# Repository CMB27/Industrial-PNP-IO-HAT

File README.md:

# Industrial PNP IO HAT+ for Raspberry Pi

Many industrial sensors, actuators, and indicator lights use 24V digital signals.
The [GPIO on the Raspberry PI 40-pin header](https://pinout.xyz/), are strictly 3.3V and not directly compatible with these devices.
This board adapts the GPIO on the Raspberry Pi to be able to interface with these higher voltage signals.

Industrial 24V signals come in two main flavors: PNP and NPN.
PNP signals are **on** when connected to 24VDC and **off** when disconnected (left floating).
NPN signals are **on** when connected to 0V (GND) and **off** when disconnected.

Where I live and work PNP signals are overwhelmingly more popular.
They are also a bit more intuitive for most people.
The digital inputs and outputs on this board are for PNP signals.

This IO board is designed to mount to DIN rail.
DIN rail is the dominant electronics mounting system in industry.
It comes in several varieties, but the most common is DIN 3 also known as "top hat".
This system is primarily designed to work with DIN 3 rail.

This board conforms to the [Raspberry Pi HAT+ specification](https://pip-assets.raspberrypi.com/categories/1215-raspberry-pi-hat/documents/RP-008281-DS-1-hat-plus-specification.pdf)

## Components

### Custom Components (The Circuit Board)
The circuit board can be ordered from [OSH Park](https://oshpark.com/shared_projects/fHu9WALf).
Gerber and Excellon drill files are also available in the gerbers folder.

### Purchased / Off-the-Shelf Components
| Ref.        | Qty. | Manufacturer    | Part Number           | Description                          | Notes                 |
| ----------: | ---: | :-------------- | :-------------------- | :----------------------------------- | :-------------------- |
| C1-C10      |   10 | KEMET           | C1206C104K5RACTU      | 0.1uF 1206 Ceramic Capacitor         |                       |
| C11         |    1 | Nichicon        | UVZ1H221MPD           | 220uF Aluminum Elecrolytic Capacitor |                       |
| D1-D12, D22 |   13 | Lite-On         | LTL2R3KGD-EM          | Green 5mm LED                        |                       |
| D13-D20     |    8 | Lite-On         | LTL2R3KRD-EM          | Red 5mm LED                          |                       |
| D21         |    1 | Lite-On         | LTL2R3KYD-EM          | Yellow 5mm LED                       |                       |
| D23         |    1 | onsemi          | MMSZ5239BT1G          | 9.1V SOD-123 Zener Diode             |                       |
| F1          |    1 | Littelfuse      | 0154005.DR            | 5A Fuse with Holder                  |                       |
| J1-J5       |    5 | Same Sky        | TBP03R1-350-12BE      | 12-Position Terminal Block Header    |                       |
| J6          |    1 | Same Sky        | TBP03R1-350-03BE      | 3-Position Terminal Block Header     |                       |
| J7          |    1 | Tensility       | 54-00167              | 5.5mm OD 2.5mm ID Barrel Jack        |                       |
| J8          |    1 | SparkFun        | PRT-14417             | QWIIC Connector                      |                       |
| J9          |    1 | Same Sky        | SSK04-FPH-254-B20     | 2x20 Socket Header                   |                       |
| P1-P5       |    5 | Same Sky        | TBP03P3-350-12BE      | 12-Position Terminal Block Plug      |                       |
| P6          |    1 | Same Sky        | TBP03P3-350-03BE      | 3-Position Terminal Block Plug       |                       |
| Q1-Q12      |   12 | onsemi          | MMUN2211LT1G          | Pre-Biased NPN SOT-23 Transistor     |                       |
| Q13         |    1 | Infineon        | IPD50P04P413ATMA2     | P-Channel TO-252 MOSFET              |                       |
| R1-R22      |   22 | YAGEO           | RC1206JR-07330RL      | 330 1206 Resistor                    |                       |
| R23         |    1 | YAGEO           | RC1206JR-071KL        | 1K 1206 Resistor                     |                       |
| R24-R26     |    3 | YAGEO           | RC1206JR-073K9L       | 3.9K 1206 Resistor                   |                       |
| R27, R28    |    2 | YAGEO           | RC1206JR-07100KL      | 100K 1206 Resistor                   |                       |
| SW1         |    1 | Same Sky        | SLW-662712-15A-SMT-TR | Slide Switch                         |                       |
| U1-U8       |    8 | Infineon        | BSP742TXUMA1          | High-Side Power Switch               |                       |
| U9          |    1 | onsemi          | CAT24C32WI-GT3        | EEPROM                               |                       |
| U10         |    1 | Analog Devices  | LTC2862AHS8-2#PBF     | RS-485 Transceiver                   |                       |
| U11         |    1 | MEAN WELL       | NID35-5               | 5V 3.5A Switching Voltage Regulator  |                       |
|             |    3 | Phoenix Contact | 1201578               | DIN Rail Adapter                     |                       |
|             |    4 | Pololu          | 1952                  | 11mm M2.5 Standoff                   | Comes in packs of 4   |
|             |    9 | McMaster-Carr   | 90380A349             | M3 x 8mm Lg. Thread-Forming Screw    | Comes in packs of 100 |
|             |    4 | McMaster-Carr   | 92005A066             | M2.5 x 6mm Lg. Pan Head Screw        | Comes in packs of 100 |
|             |    4 | McMaster-Catt   | 90591A270             | M2.5 Hex Nut                         | Comes in packs of 100 |

### 24VDC Power Supply
While not considered to be a part of this design, a 24V power supply will be needed to power the IO board.
It should be able to output at least 3A.
A suggested model is MEAN WELL `GST90A24-P1M`.
This model will also require a power cable; if you are in North America, Tensility `11-00022` should work.
The IO board has a built in fuse on its power input so an external fuse or circuit breaker is not needed.

### Raspberry Pi
You will also need a Raspberry Pi and SD card with an operating system (OS) loaded on it to make it function.
See the official Raspberry Pi [getting started](https://www.raspberrypi.com/documentation/computers/getting-started.html) documentation for details.
The IO board powers the Raspberry Pi, so a USB power supply is not needed.

### Replacement Fuse
If you happen to blow the fuse, the replacement part is Littelfuse `0451005.MRL`.

## Tools and Supplies
Various methods can be used to assemble this board.
The list of tools and supplies below is for the hand soldering method.

- A good soldering iron, preferably with temperature control - Please do not try to use a $5 soldering iron; these tend to have to overall effect of just making people hate soldering.
- Tweezers
- Solder - Leaded is easier to work with, but it's, well... leaded.
- Flux (optional) - I say optional, but if you are using lead-free solder, I would get it.
- Solder wick (optional) - If you anticipate screwing something up while soldering, this will help to fix things.
- Smoke absorber (optional) - I'm a non-smoker; I'd like to remain that way.
- A Phillips No.1 screwdriver
- A 5mm wrench

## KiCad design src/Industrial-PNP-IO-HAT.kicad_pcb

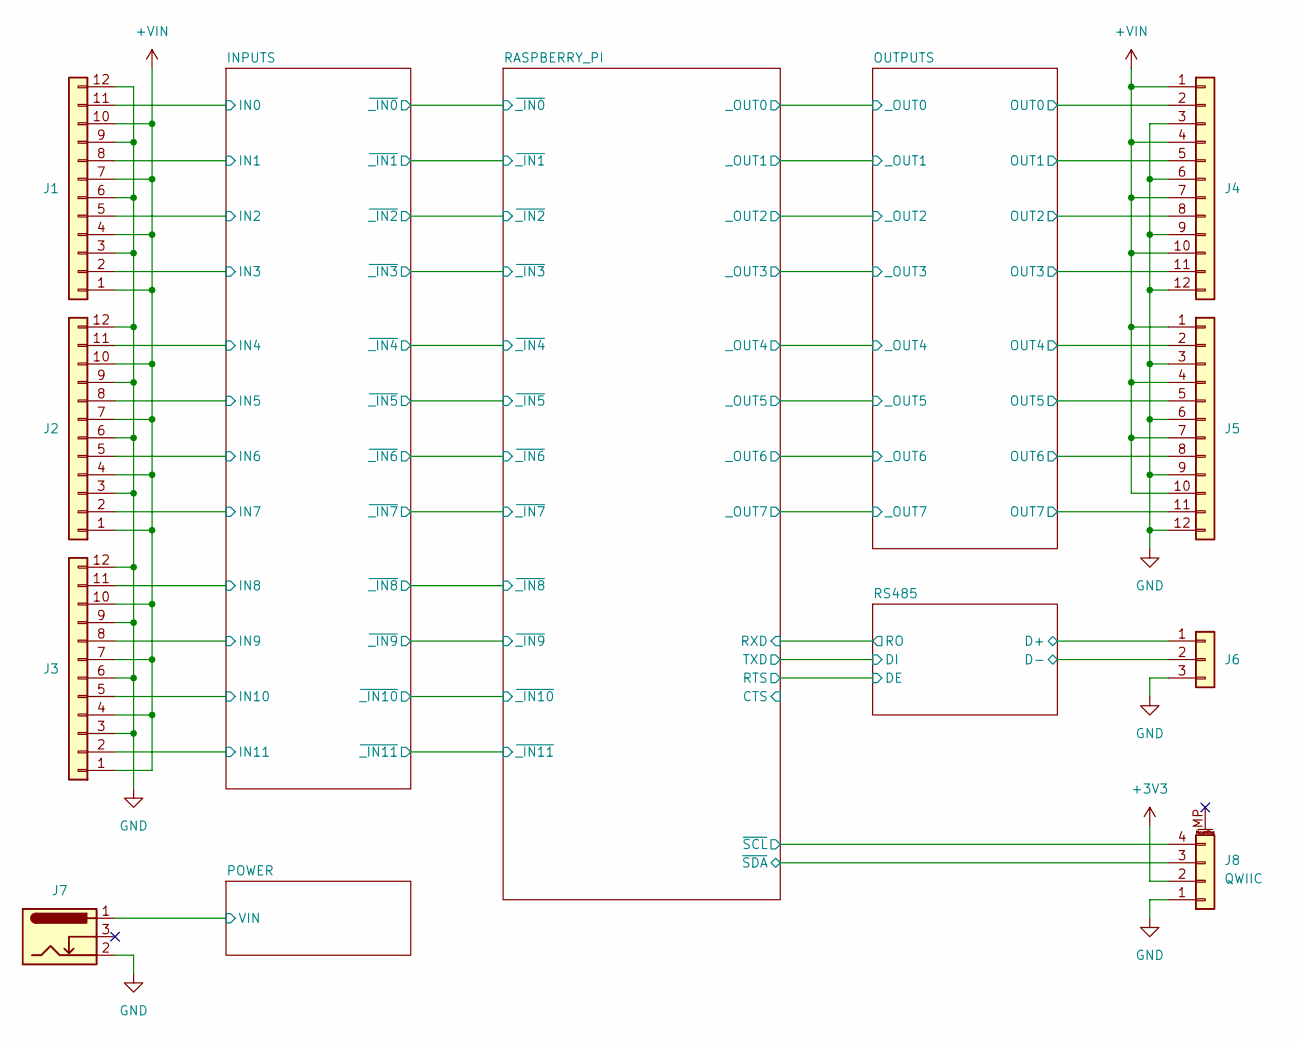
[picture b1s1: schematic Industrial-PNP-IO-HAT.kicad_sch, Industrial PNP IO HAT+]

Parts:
J1, J2, J3, J4, J5: Conn_01x12; TerminalBlockHeader_1x12_P3.5_Horizontal_IO; Part Number TBP03R1-350-12BE
J6: Conn_01x03; TerminalBlockHeader_1x3_P3.5_Horizontal_RS485; Part Number TBP03R1-350-03BE
J7: Barrel_Jack_Switch; Tensility_54-00167; Part Number 54-00167
J8: QWIIC; JST_SH_SM04B-SRSS-TB_1x04-1MP_P1.00mm_Horizontal; Part Number PRT-14417

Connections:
+3V3: J8.2; also elsewhere on the board
+VIN: J1.1, J1.4, J1.7, J1.10, J2.1, J2.4, J2.7, J2.10, J3.1, J3.4, J3.7, J3.10, J4.1, J4.4, J4.7, J4.10, J5.1, J5.4, J5.7, J5.10; also elsewhere on the board
/INPUTS/IN0: J1.11; also elsewhere on the board
/INPUTS/IN1: J1.8; also elsewhere on the board
/INPUTS/IN2: J1.5; also elsewhere on the board
/INPUTS/IN3: J1.2; also elsewhere on the board
/INPUTS/IN4: J2.11; also elsewhere on the board
/INPUTS/IN5: J2.8; also elsewhere on the board
/INPUTS/IN6: J2.5; also elsewhere on the board
/INPUTS/IN7: J2.2; also elsewhere on the board
/INPUTS/IN8: J3.11; also elsewhere on the board
/INPUTS/IN9: J3.8; also elsewhere on the board
/INPUTS/IN10: J3.5; also elsewhere on the board
/INPUTS/IN11: J3.2; also elsewhere on the board
/OUTPUTS/OUT0: J4.2; also elsewhere on the board
/OUTPUTS/OUT1: J4.5; also elsewhere on the board
/OUTPUTS/OUT2: J4.8; also elsewhere on the board
/OUTPUTS/OUT3: J4.11; also elsewhere on the board
/OUTPUTS/OUT4: J5.2; also elsewhere on the board
/OUTPUTS/OUT5: J5.5; also elsewhere on the board
/OUTPUTS/OUT6: J5.8; also elsewhere on the board
/OUTPUTS/OUT7: J5.11; also elsewhere on the board
/POWER/VIN: J7.1; also elsewhere on the board
/RASPBERRY_PI/~SCL: J8.4; also elsewhere on the board
/RASPBERRY_PI/~SDA: J8.3; also elsewhere on the board
/RS485/D+: J6.1; also elsewhere on the board
/RS485/D-: J6.2; also elsewhere on the board
GND: J1.3, J1.6, J1.9, J1.12, J2.3, J2.6, J2.9, J2.12, J3.3, J3.6, J3.9, J3.12, J4.3, J4.6, J4.9, J4.12, J5.3, J5.6, J5.9, J5.12, J6.3, J7.2, J8.1; also elsewhere on the board

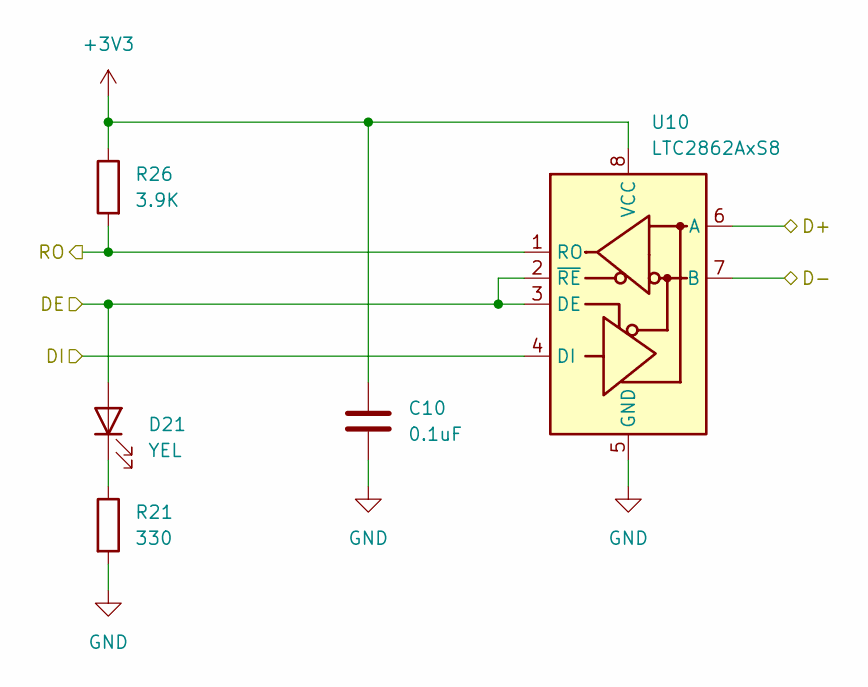
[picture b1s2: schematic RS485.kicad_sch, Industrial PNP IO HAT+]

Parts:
C10: 0.1uF; C_1206_3216Metric_Pad1.33x1.80mm_HandSolder; Part Number C1206C104K5RACTU
D21: YEL; LED_5mm_Yellow; Part Number LTL2R3KYD-EM
R21: 330; R_1206_3216Metric_Pad1.30x1.75mm_HandSolder; Part Number RC1206JR-07330RL
R26: 3.9K; R_1206_3216Metric_Pad1.30x1.75mm_HandSolder; Part Number RC1206JR-073K9L
U10: LTC2862AxS8; SOIC-8_3.9x4.9mm_P1.27mm; Part Number LTC2862AHS8-2#PBF

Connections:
+3V3: C10.1, R26.1, U10.8 (VCC); also elsewhere on the board
/RASPBERRY_PI/RTS: D21.2 (A), U10.2 (~RE), U10.3 (DE); also elsewhere on the board
/RASPBERRY_PI/RXD: R26.2, U10.1 (RO); also elsewhere on the board
/RASPBERRY_PI/TXD: U10.4 (DI); also elsewhere on the board
/RS485/D+: U10.6 (A); also elsewhere on the board
/RS485/D-: U10.7 (B); also elsewhere on the board
GND: C10.2, R21.2, U10.5 (GND); also elsewhere on the board
unnamed: D21.1 (K), R21.1

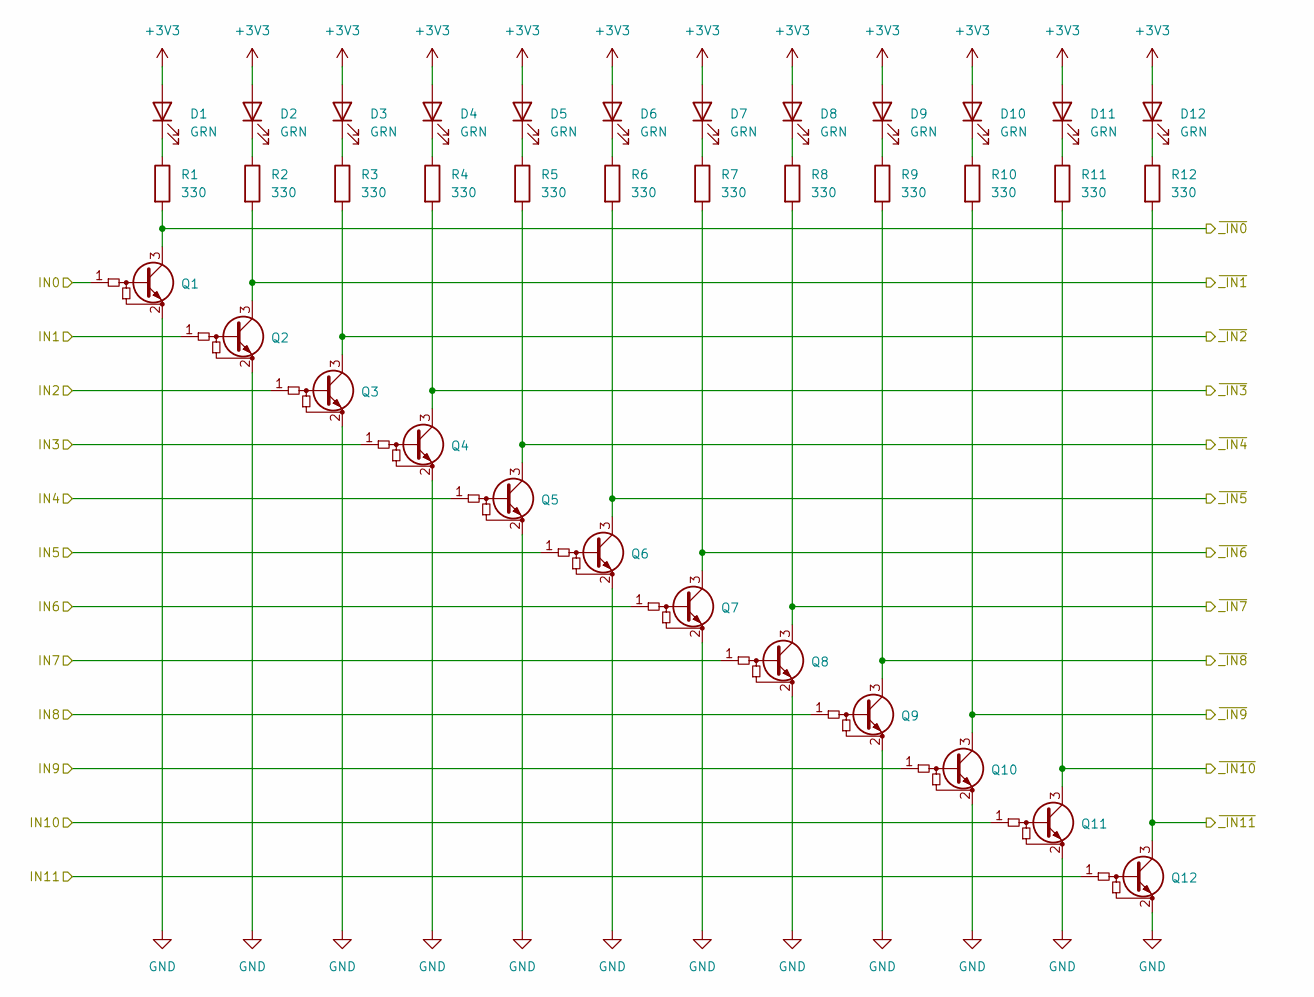
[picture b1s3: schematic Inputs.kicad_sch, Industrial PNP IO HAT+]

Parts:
D1, D2, D3, D4, D5, D6, D7, D8, D9, D10, D11, D12: GRN; LED_5mm_Green; Part Number LTL2R3KGD-EM
Q1, Q2, Q3, Q4, Q5, Q6, Q7, Q8, Q9, Q10, Q11, Q12: Q_NPN_BRT_BEC; SOT-23; Part Number MMUN2211LT1G
R1, R2, R3, R4, R5, R6, R7, R8, R9, R10, R11, R12: 330; R_1206_3216Metric_Pad1.30x1.75mm_HandSolder; Part Number RC1206JR-07330RL

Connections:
+3V3: D1.2 (A), D2.2 (A), D3.2 (A), D4.2 (A), D5.2 (A), D6.2 (A), D7.2 (A), D8.2 (A), D9.2 (A), D10.2 (A), D11.2 (A), D12.2 (A); also elsewhere on the board
/INPUTS/IN0: Q1.1 (B); also elsewhere on the board
/INPUTS/IN1: Q2.1 (B); also elsewhere on the board
/INPUTS/IN2: Q3.1 (B); also elsewhere on the board
/INPUTS/IN3: Q4.1 (B); also elsewhere on the board
/INPUTS/IN4: Q5.1 (B); also elsewhere on the board
/INPUTS/IN5: Q6.1 (B); also elsewhere on the board
/INPUTS/IN6: Q7.1 (B); also elsewhere on the board
/INPUTS/IN7: Q8.1 (B); also elsewhere on the board
/INPUTS/IN8: Q9.1 (B); also elsewhere on the board
/INPUTS/IN9: Q10.1 (B); also elsewhere on the board
/INPUTS/IN10: Q11.1 (B); also elsewhere on the board
/INPUTS/IN11: Q12.1 (B); also elsewhere on the board
/INPUTS/~_IN0: Q1.3 (C), R1.2; also elsewhere on the board
/INPUTS/~_IN1: Q2.3 (C), R2.2; also elsewhere on the board
/INPUTS/~_IN2: Q3.3 (C), R3.2; also elsewhere on the board
/INPUTS/~_IN3: Q4.3 (C), R4.2; also elsewhere on the board
/INPUTS/~_IN4: Q5.3 (C), R5.2; also elsewhere on the board
/INPUTS/~_IN5: Q6.3 (C), R6.2; also elsewhere on the board
/INPUTS/~_IN6: Q7.3 (C), R7.2; also elsewhere on the board
/INPUTS/~_IN7: Q8.3 (C), R8.2; also elsewhere on the board
/INPUTS/~_IN8: Q9.3 (C), R9.2; also elsewhere on the board
/INPUTS/~_IN9: Q10.3 (C), R10.2; also elsewhere on the board
/INPUTS/~_IN10: Q11.3 (C), R11.2; also elsewhere on the board
/INPUTS/~_IN11: Q12.3 (C), R12.2; also elsewhere on the board
GND: Q1.2 (E), Q2.2 (E), Q3.2 (E), Q4.2 (E), Q5.2 (E), Q6.2 (E), Q7.2 (E), Q8.2 (E), Q9.2 (E), Q10.2 (E), Q11.2 (E), Q12.2 (E); also elsewhere on the board
unnamed: D1.1 (K), R1.1
unnamed: D2.1 (K), R2.1
unnamed: D3.1 (K), R3.1
unnamed: D4.1 (K), R4.1
unnamed: D5.1 (K), R5.1
unnamed: D6.1 (K), R6.1
unnamed: D7.1 (K), R7.1
unnamed: D8.1 (K), R8.1
unnamed: D9.1 (K), R9.1
unnamed: D10.1 (K), R10.1
unnamed: D11.1 (K), R11.1
unnamed: D12.1 (K), R12.1

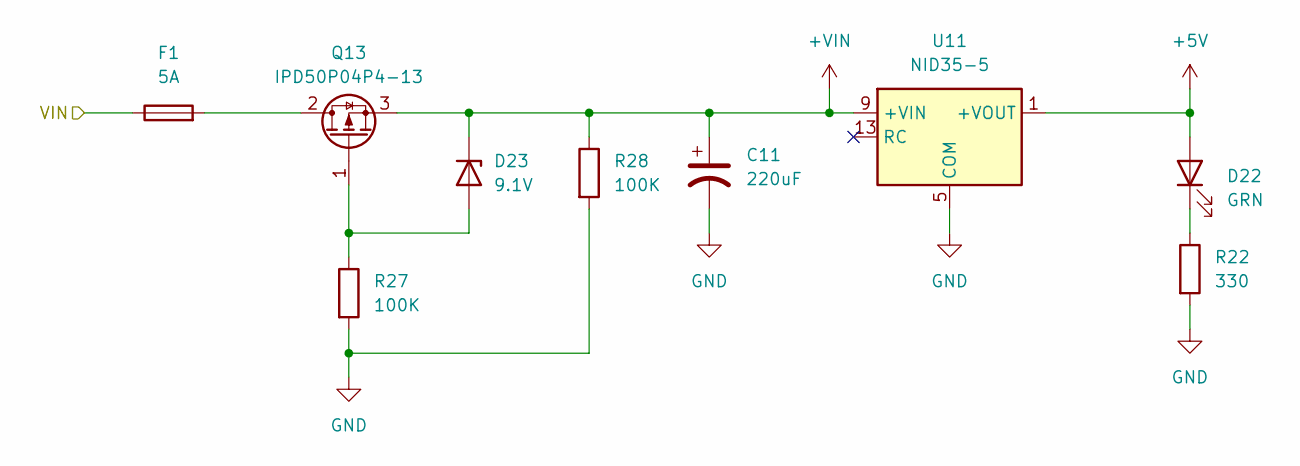
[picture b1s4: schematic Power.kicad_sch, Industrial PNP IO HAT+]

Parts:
C11: 220uF; CP_Radial_D10.0mm_P5.00mm; Part Number UVZ1H221MPD
D22: GRN; LED_5mm_Green; Part Number LTL2R3KGD-EM
D23: 9.1V; D_SOD-123; Part Number MMSZ5239BT1G
F1: 5A; Fuseholder_Littelfuse_Nano2_154x; Part Number 0154005.DR
Q13: IPD50P04P4-13; TO-252-2; Part Number IPD50P04P413ATMA2
R22: 330; R_1206_3216Metric_Pad1.30x1.75mm_HandSolder; Part Number RC1206JR-07330RL
R27, R28: 100K; R_1206_3216Metric_Pad1.30x1.75mm_HandSolder; Part Number RC1206JR-07100KL
U11: NID35-5; MEAN_WELL_NID100; Part Number NID35-5

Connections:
+5V: D22.2 (A), U11.1 (+VOUT), U11.2 (+VOUT), U11.3 (+VOUT), U11.4 (+VOUT); also elsewhere on the board
+VIN: C11.1, D23.1 (K), Q13.3 (S), R28.1, U11.9 (+VIN), U11.10 (+VIN); also elsewhere on the board
/POWER/VIN: F1.1; also elsewhere on the board
GND: C11.2, R22.2, R27.2, R28.2, U11.5 (COM), U11.6 (COM), U11.7 (COM), U11.8 (COM); also elsewhere on the board
unnamed: D22.1 (K), R22.1
unnamed: D23.2 (A), Q13.1 (G), R27.1
unnamed: F1.2, Q13.2 (D)

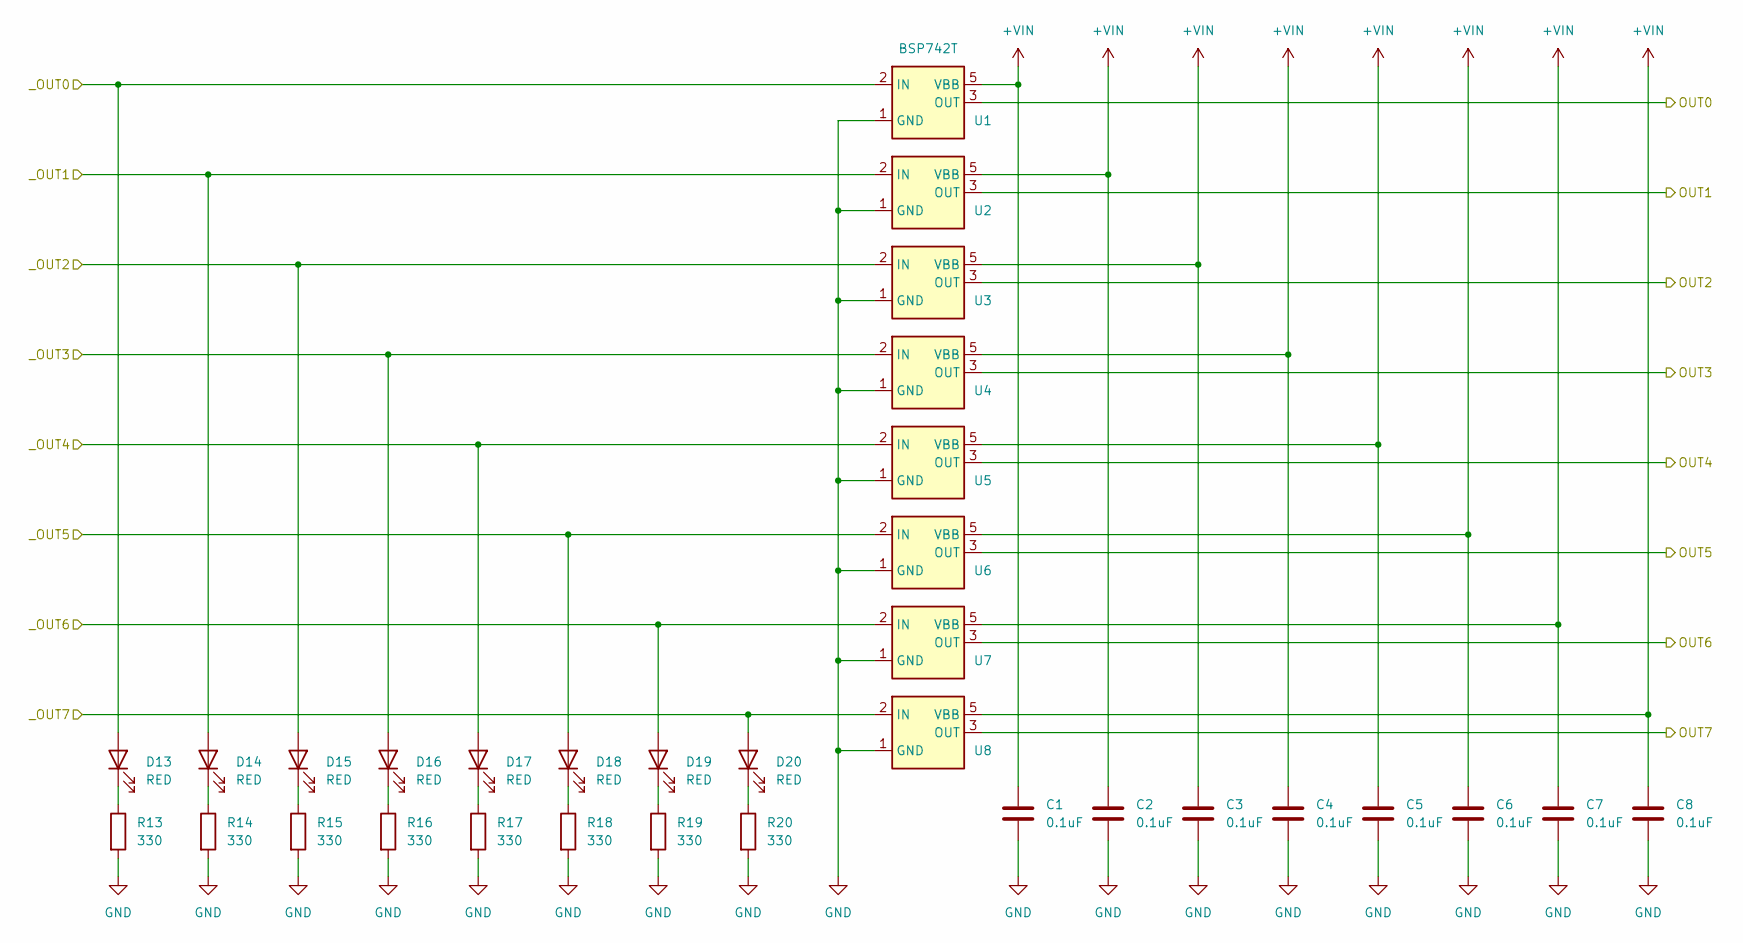
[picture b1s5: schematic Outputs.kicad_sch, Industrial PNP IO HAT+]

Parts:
C1, C2, C3, C4, C5, C6, C7, C8: 0.1uF; C_1206_3216Metric_Pad1.33x1.80mm_HandSolder; Part Number C1206C104K5RACTU
D13, D14, D15, D16, D17, D18, D19, D20: RED; LED_5mm_Red; Part Number LTL2R3KRD-EM
R13, R14, R15, R16, R17, R18, R19, R20: 330; R_1206_3216Metric_Pad1.30x1.75mm_HandSolder; Part Number RC1206JR-07330RL
U1, U2, U3, U4, U5, U6, U7, U8: BSP742T; SOIC-8_3.9x4.9mm_P1.27mm; Part Number BSP742TXUMA1

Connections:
+VIN: C1.1, C2.1, C3.1, C4.1, C5.1, C6.1, C7.1, C8.1, U1.5 (VBB), U1.6 (VBB), U1.7 (VBB), U1.8 (VBB), U2.5 (VBB), U2.6 (VBB), U2.7 (VBB), U2.8 (VBB), U3.5 (VBB), U3.6 (VBB), U3.7 (VBB), U3.8 (VBB), U4.5 (VBB), U4.6 (VBB), U4.7 (VBB), U4.8 (VBB), U5.5 (VBB), U5.6 (VBB), U5.7 (VBB), U5.8 (VBB), U6.5 (VBB), U6.6 (VBB), U6.7 (VBB), U6.8 (VBB), U7.5 (VBB), U7.6 (VBB), U7.7 (VBB), U7.8 (VBB), U8.5 (VBB), U8.6 (VBB), U8.7 (VBB), U8.8 (VBB); also elsewhere on the board
/OUTPUTS/OUT0: U1.3 (OUT); also elsewhere on the board
/OUTPUTS/OUT1: U2.3 (OUT); also elsewhere on the board
/OUTPUTS/OUT2: U3.3 (OUT); also elsewhere on the board
/OUTPUTS/OUT3: U4.3 (OUT); also elsewhere on the board
/OUTPUTS/OUT4: U5.3 (OUT); also elsewhere on the board
/OUTPUTS/OUT5: U6.3 (OUT); also elsewhere on the board
/OUTPUTS/OUT6: U7.3 (OUT); also elsewhere on the board
/OUTPUTS/OUT7: U8.3 (OUT); also elsewhere on the board
/OUTPUTS/_OUT0: D13.2 (A), U1.2 (IN); also elsewhere on the board
/OUTPUTS/_OUT1: D14.2 (A), U2.2 (IN); also elsewhere on the board
/OUTPUTS/_OUT2: D15.2 (A), U3.2 (IN); also elsewhere on the board
/OUTPUTS/_OUT3: D16.2 (A), U4.2 (IN); also elsewhere on the board
/OUTPUTS/_OUT4: D17.2 (A), U5.2 (IN); also elsewhere on the board
/OUTPUTS/_OUT5: D18.2 (A), U6.2 (IN); also elsewhere on the board
/OUTPUTS/_OUT6: D19.2 (A), U7.2 (IN); also elsewhere on the board
/OUTPUTS/_OUT7: D20.2 (A), U8.2 (IN); also elsewhere on the board
GND: C1.2, C2.2, C3.2, C4.2, C5.2, C6.2, C7.2, C8.2, R13.2, R14.2, R15.2, R16.2, R17.2, R18.2, R19.2, R20.2, U1.1 (GND), U2.1 (GND), U3.1 (GND), U4.1 (GND), U5.1 (GND), U6.1 (GND), U7.1 (GND), U8.1 (GND); also elsewhere on the board
unnamed: D13.1 (K), R13.1
unnamed: D14.1 (K), R14.1
unnamed: D15.1 (K), R15.1
unnamed: D16.1 (K), R16.1
unnamed: D17.1 (K), R17.1
unnamed: D18.1 (K), R18.1
unnamed: D19.1 (K), R19.1
unnamed: D20.1 (K), R20.1

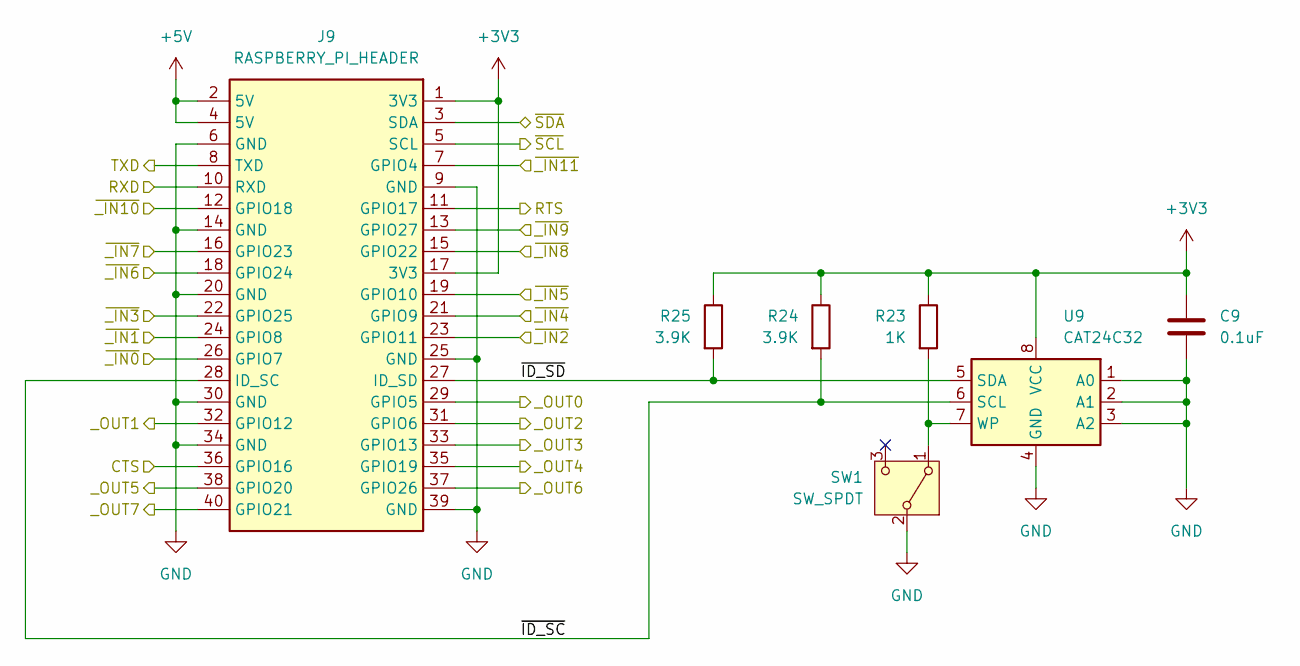
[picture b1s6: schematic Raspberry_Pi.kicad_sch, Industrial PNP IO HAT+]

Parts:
C9: 0.1uF; C_1206_3216Metric_Pad1.33x1.80mm_HandSolder; Part Number C1206C104K5RACTU
J9: RASPBERRY_PI_HEADER; Raspberry_Pi_Generic; Part Number SSK04-FPH-254-B20
R23: 1K; R_1206_3216Metric_Pad1.30x1.75mm_HandSolder; Part Number RC1206JR-071KL
R24, R25: 3.9K; R_1206_3216Metric_Pad1.30x1.75mm_HandSolder; Part Number RC1206JR-073K9L
SW1: SW_SPDT; SW_SPDT_PCM12; Part Number SLW-662712-15A-SMT-TR
U9: CAT24C32; SOIC-8_3.9x4.9mm_P1.27mm; Part Number CAT24C32WI-GT3

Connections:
+3V3: C9.1, J9.1 (3V3), J9.17 (3V3), R23.1, R24.1, R25.1, U9.8 (VCC); also elsewhere on the board
+5V: J9.2 (5V), J9.4 (5V); also elsewhere on the board
/INPUTS/~_IN0: J9.26 (GPIO7); also elsewhere on the board
/INPUTS/~_IN1: J9.24 (GPIO8); also elsewhere on the board
/INPUTS/~_IN2: J9.23 (GPIO11); also elsewhere on the board
/INPUTS/~_IN3: J9.22 (GPIO25); also elsewhere on the board
/INPUTS/~_IN4: J9.21 (GPIO9); also elsewhere on the board
/INPUTS/~_IN5: J9.19 (GPIO10); also elsewhere on the board
/INPUTS/~_IN6: J9.18 (GPIO24); also elsewhere on the board
/INPUTS/~_IN7: J9.16 (GPIO23); also elsewhere on the board
/INPUTS/~_IN8: J9.15 (GPIO22); also elsewhere on the board
/INPUTS/~_IN9: J9.13 (GPIO27); also elsewhere on the board
/INPUTS/~_IN10: J9.12 (GPIO18); also elsewhere on the board
/INPUTS/~_IN11: J9.7 (GPIO4); also elsewhere on the board
/OUTPUTS/_OUT0: J9.29 (GPIO5); also elsewhere on the board
/OUTPUTS/_OUT1: J9.32 (GPIO12); also elsewhere on the board
/OUTPUTS/_OUT2: J9.31 (GPIO6); also elsewhere on the board
/OUTPUTS/_OUT3: J9.33 (GPIO13); also elsewhere on the board
/OUTPUTS/_OUT4: J9.35 (GPIO19); also elsewhere on the board
/OUTPUTS/_OUT5: J9.38 (GPIO20); also elsewhere on the board
/OUTPUTS/_OUT6: J9.37 (GPIO26); also elsewhere on the board
/OUTPUTS/_OUT7: J9.40 (GPIO21); also elsewhere on the board
/RASPBERRY_PI/CTS: J9.36 (GPIO16)
/RASPBERRY_PI/RTS: J9.11 (GPIO17); also elsewhere on the board
/RASPBERRY_PI/RXD: J9.10 (RXD); also elsewhere on the board
/RASPBERRY_PI/TXD: J9.8 (TXD); also elsewhere on the board
/RASPBERRY_PI/~ID_SC: J9.28 (ID_SC), R24.2, U9.6 (SCL)
/RASPBERRY_PI/~ID_SD: J9.27 (ID_SD), R25.2, U9.5 (SDA)
/RASPBERRY_PI/~SCL: J9.5 (SCL); also elsewhere on the board
/RASPBERRY_PI/~SDA: J9.3 (SDA); also elsewhere on the board
GND: C9.2, J9.6 (GND), J9.9 (GND), J9.14 (GND), J9.20 (GND), J9.25 (GND), J9.30 (GND), J9.34 (GND), J9.39 (GND), SW1.2 (B), U9.1 (A0), U9.2 (A1), U9.3 (A2), U9.4 (GND); also elsewhere on the board
unnamed: R23.2, SW1.1 (A), U9.7 (WP)

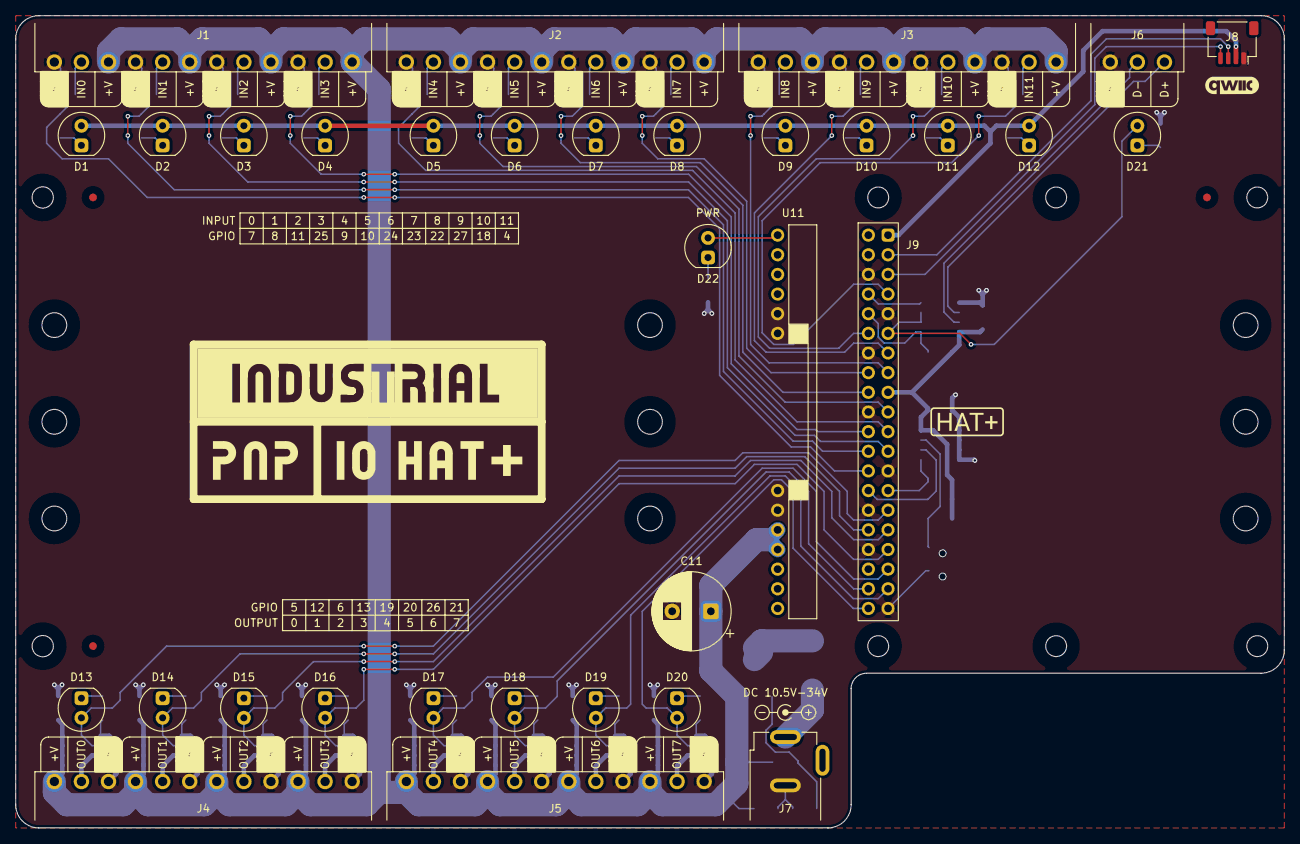
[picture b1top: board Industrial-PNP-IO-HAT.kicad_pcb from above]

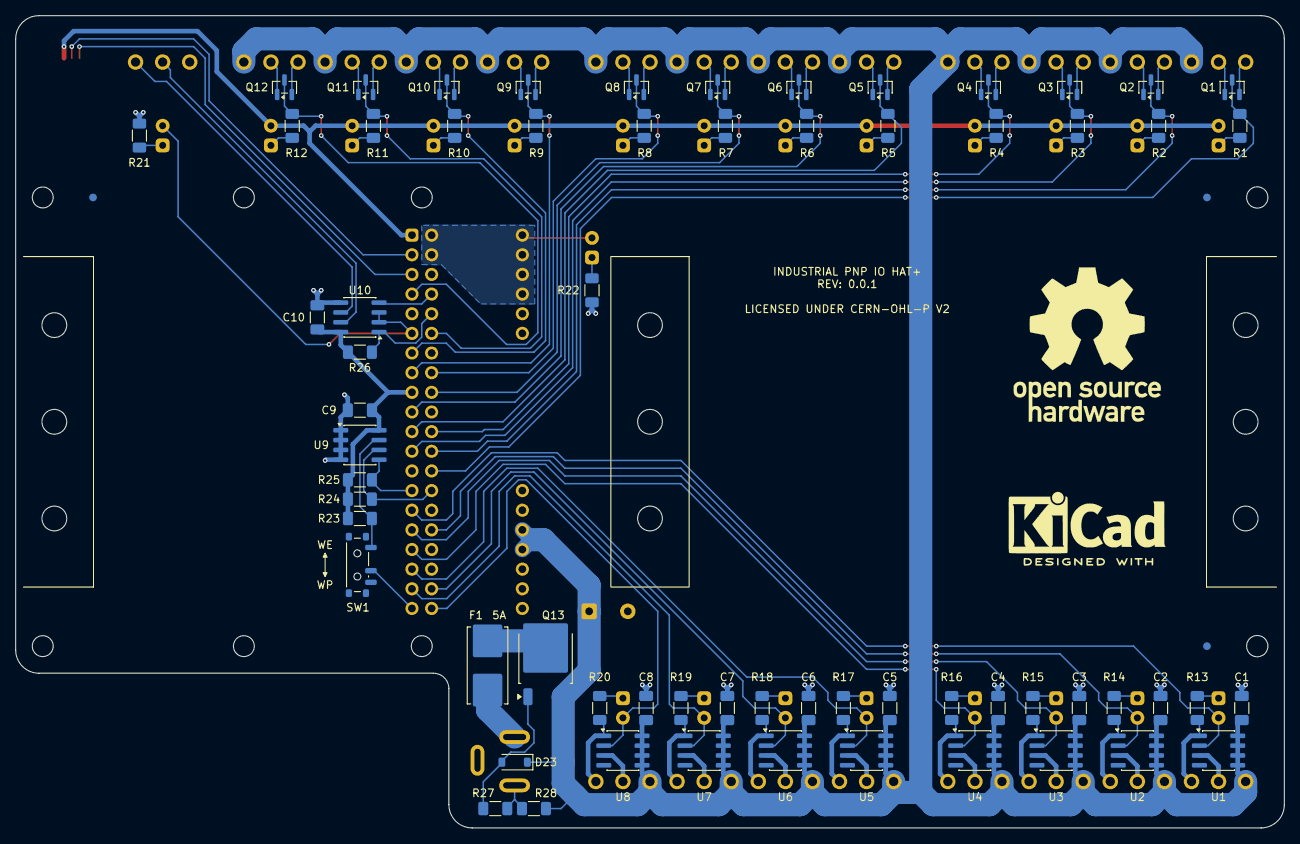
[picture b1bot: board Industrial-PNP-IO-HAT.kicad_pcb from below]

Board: 2 copper layers, 164.0 x 105.0 mm, 97 parts (64 on the bottom side), 79 nets.

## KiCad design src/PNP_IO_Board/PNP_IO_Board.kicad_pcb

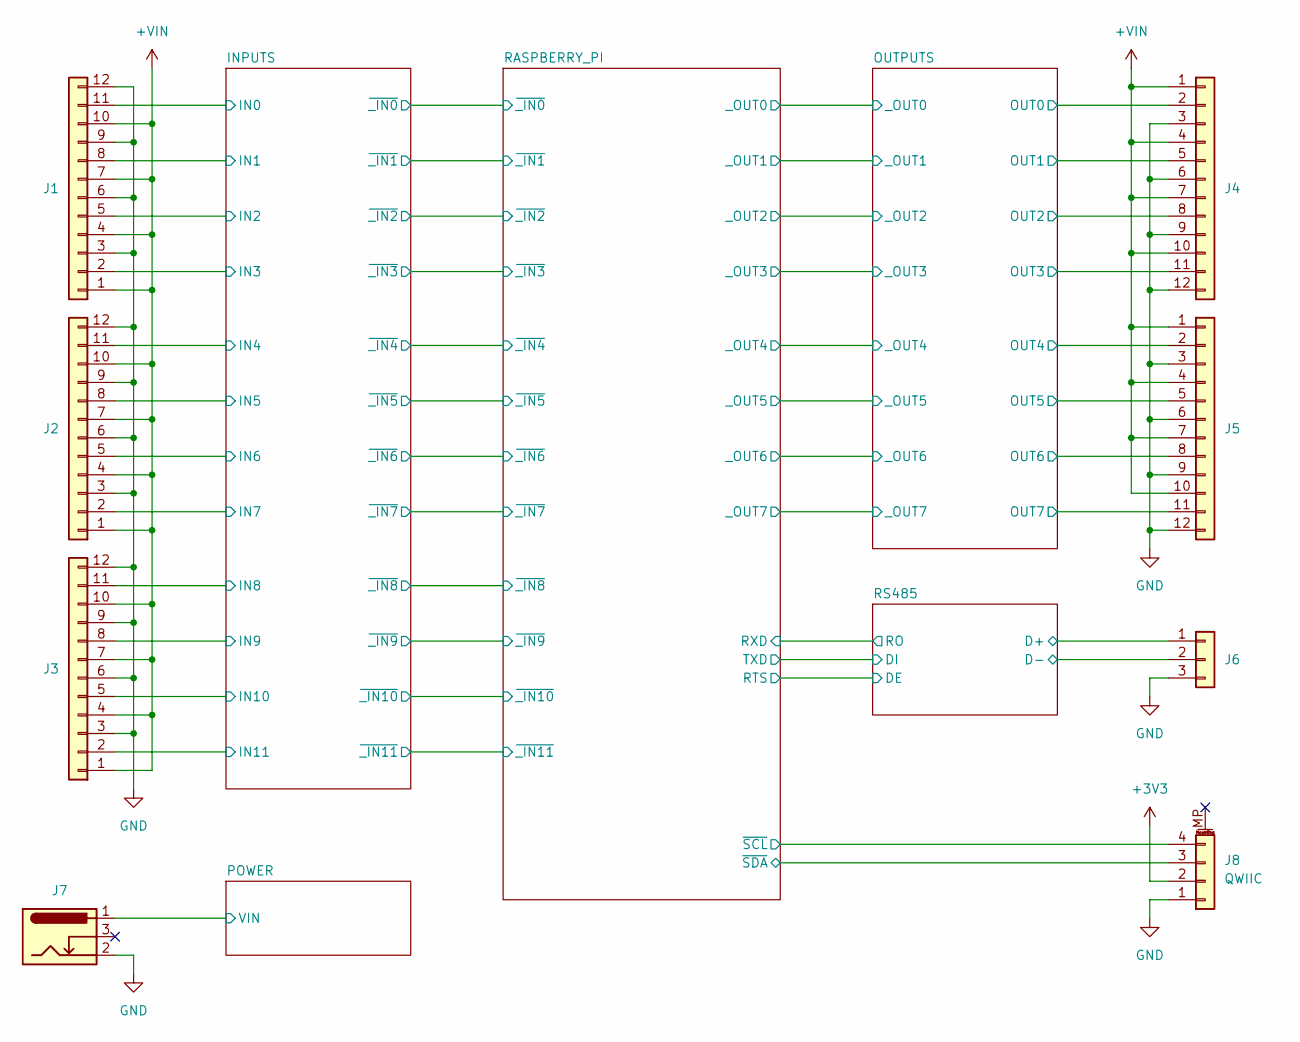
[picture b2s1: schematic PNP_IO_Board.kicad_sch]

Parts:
J1, J2, J3, J4, J5: Conn_01x12; TerminalBlockHeader_1x12_P3.5_Horizontal_IO
J6: Conn_01x03; TerminalBlockHeader_1x3_P3.5_Horizontal_RS485
J7: Barrel_Jack_Switch; BarrelJack_Horizontal; Part Number 54-00167
J8: QWIIC; JST_SH_SM04B-SRSS-TB_1x04-1MP_P1.00mm_Horizontal

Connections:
+3V3: J8.2; also elsewhere on the board
+VIN: J1.1, J1.4, J1.7, J1.10, J2.1, J2.4, J2.7, J2.10, J3.1, J3.4, J3.7, J3.10, J4.1, J4.4, J4.7, J4.10, J5.1, J5.4, J5.7, J5.10; also elsewhere on the board
/INPUTS/IN0: J1.11; also elsewhere on the board
/INPUTS/IN1: J1.8; also elsewhere on the board
/INPUTS/IN2: J1.5; also elsewhere on the board
/INPUTS/IN3: J1.2; also elsewhere on the board
/INPUTS/IN4: J2.11; also elsewhere on the board
/INPUTS/IN5: J2.8; also elsewhere on the board
/INPUTS/IN6: J2.5; also elsewhere on the board
/INPUTS/IN7: J2.2; also elsewhere on the board
/INPUTS/IN8: J3.11; also elsewhere on the board
/INPUTS/IN9: J3.8; also elsewhere on the board
/INPUTS/IN10: J3.5; also elsewhere on the board
/INPUTS/IN11: J3.2; also elsewhere on the board
/OUTPUTS/OUT0: J4.2; also elsewhere on the board
/OUTPUTS/OUT1: J4.5; also elsewhere on the board
/OUTPUTS/OUT2: J4.8; also elsewhere on the board
/OUTPUTS/OUT3: J4.11; also elsewhere on the board
/OUTPUTS/OUT4: J5.2; also elsewhere on the board
/OUTPUTS/OUT5: J5.5; also elsewhere on the board
/OUTPUTS/OUT6: J5.8; also elsewhere on the board
/OUTPUTS/OUT7: J5.11; also elsewhere on the board
/POWER/VIN: J7.1; also elsewhere on the board
/RASPBERRY_PI/~SCL: J8.4; also elsewhere on the board
/RASPBERRY_PI/~SDA: J8.3; also elsewhere on the board
/RS485/D+: J6.1; also elsewhere on the board
/RS485/D-: J6.2; also elsewhere on the board
GND: J1.3, J1.6, J1.9, J1.12, J2.3, J2.6, J2.9, J2.12, J3.3, J3.6, J3.9, J3.12, J4.3, J4.6, J4.9, J4.12, J5.3, J5.6, J5.9, J5.12, J6.3, J7.2, J8.1; also elsewhere on the board

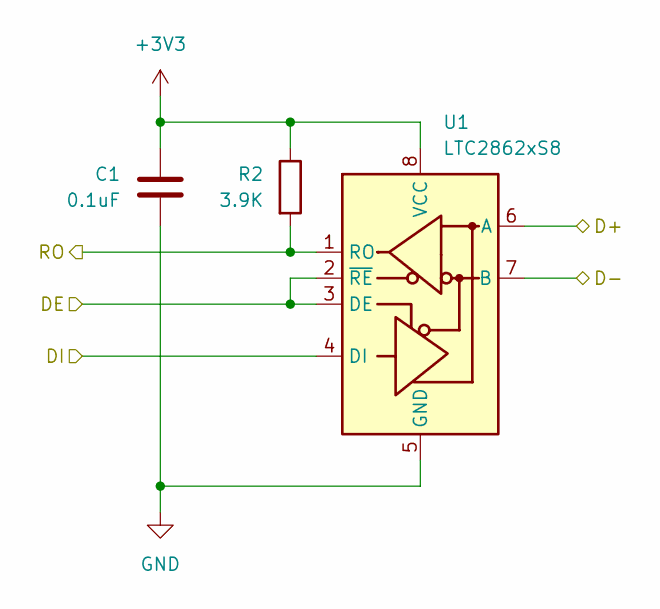
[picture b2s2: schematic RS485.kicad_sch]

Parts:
C1: 0.1uF; C_1206_3216Metric_Pad1.33x1.80mm_HandSolder
R2: 3.9K; R_1206_3216Metric_Pad1.30x1.75mm_HandSolder
U1: LTC2862xS8; SOIC-8_3.9x4.9mm_P1.27mm

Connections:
+3V3: C1.1, R2.1, U1.8 (VCC); also elsewhere on the board
/RASPBERRY_PI/RTS: U1.2 (~RE), U1.3 (DE); also elsewhere on the board
/RASPBERRY_PI/RXD: R2.2, U1.1 (RO); also elsewhere on the board
/RASPBERRY_PI/TXD: U1.4 (DI); also elsewhere on the board
/RS485/D+: U1.6 (A); also elsewhere on the board
/RS485/D-: U1.7 (B); also elsewhere on the board
GND: C1.2, U1.5 (GND); also elsewhere on the board

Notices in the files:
src/Industrial-PNP-IO-HAT.kicad_pcb:
© 2026 C. M. Bulliner. Released under the CERN-OHL-P v2 license.
LICENSED UNDER CERN-OHL-P V2
